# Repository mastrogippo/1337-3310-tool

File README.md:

## Nokia 3310 converted to a multitool
### More info:

http://hackaday.io/project/3472-1337-3310-tool

http://www.mastrogippo.it/

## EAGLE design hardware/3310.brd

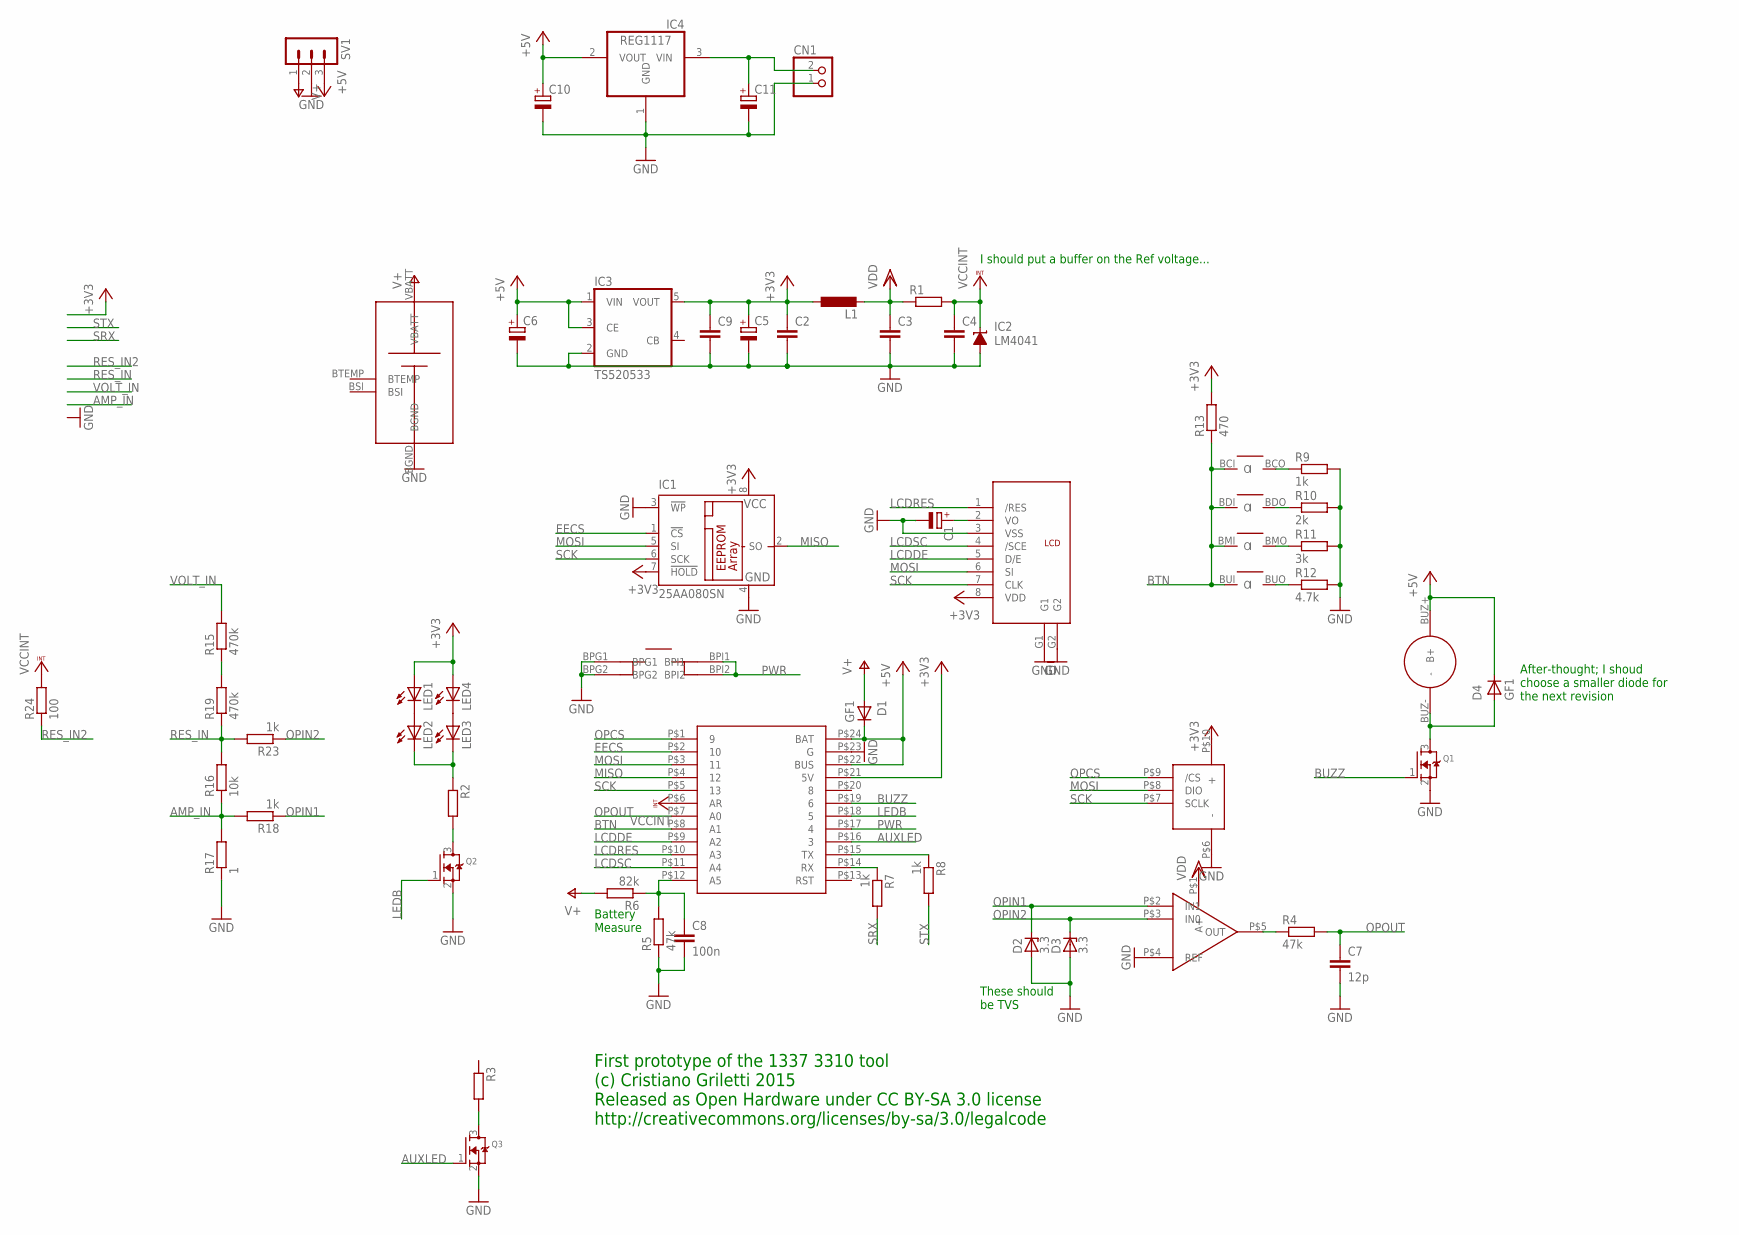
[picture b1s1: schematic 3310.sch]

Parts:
C1: CPOL-EUC/6032-28R; C/6032-28R
C2, C3, C4, C9: C-EUC0805K; C0805K
C5, C6, C10, C11: CPOL-EUB/3528-21R; B/3528-21R
C7: 12p; C0805K
C8: 100n; C0805K
CN1: JST_2PIN-SMT; JST-PH-2-SMT
D1, D4: GF1; SMA-DO214AC
D2, D3: 3.3; SOD80C
IC1: 25AA080SN; SO-08
IC2: LM4041; DBZ_R-PDSO-G3
IC3: TS520533; SOT25
IC4: REG1117; SOT223
L1: L-EUL3216C; L3216C
LED1, LED2, LED3, LED4: LEDCHIPLED_0603; CHIPLED_0603
Q1, Q2, Q3: MOSFET-NREFLOW; SOT23
R1, R2, R3: R-EU_R0805; R0805
R4, R5: 47k; R0805
R6: 82k; R0805
R7, R8, R9, R18, R23: 1k; R0805
R10: 2k; R0805
R11: 3k; R0805
R12: 4.7k; R0805
R13: 470; R0805
R15, R19: 470k; R0805
R16: 10k; R0805
R17: 1; R0805
R24: 100; R0805
SV1: MA03-1
U$1: 3310PANEL_NONUM; 3310BRD_NONUM
U$2: PGA113; VSSOP
U$3: TRINKET

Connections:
+3V3: C2.1, C5.+, C9.1, IC1.7 (!HOLD), IC1.8 (VCC), IC3.5 (VOUT), L1.1, LED1.A, LED4.A, R13.2, U$1.8 (VDD), U$2.P$10 (+), U$3.P$21 (5V)
+5V: C6.+, C10.+, D1.K (C), D4.K (C), IC3.1 (VIN), IC3.3 (CE), IC4.2 (VOUT), SV1.3, U$1.BUZ+ (B+), U$3.P$22 (BUS), U$3.P$24 (BAT)
AMP_IN: R16.1, R17.2, R18.2
AUXLED: Q3.1 (G), U$3.P$16 (3)
BTN: R13.1, U$1.BCI (I), U$1.BDI (I), U$1.BMI (I), U$1.BUI (I), U$3.P$8 (A1)
BUZZ: Q1.1 (G), U$3.P$19 (6)
EECS: IC1.1 (!CS), U$3.P$2 (10)
GND: C1.-, C2.2, C3.2, C4.2, C5.-, C6.-, C7.2, C8.2, C9.2, C10.-, C11.-, CN1.1 (2), D2.A, D3.A, IC1.3 (!WP), IC1.4 (GND), IC2.2 (A), IC3.2 (GND), IC4.1 (GND), Q1.2 (S), Q2.2 (S), Q3.2 (S), R5.1, R9.2, R10.2, R11.2, R12.2, R17.1, SV1.2, U$1.3 (VSS), U$1.BGND, U$1.BPG1, U$1.BPG2, U$1.G1, U$1.G2, U$2.P$4 (REF), U$2.P$6 (-), U$3.P$23 (G)
LCDDE: U$1.5 (D/E), U$3.P$9 (A2)
LCDRES: U$1.1 (/RES), U$3.P$10 (A3)
LCDSC: U$1.4 (/SCE), U$3.P$11 (A4)
LEDB: Q2.1 (G), U$3.P$18 (5)
MISO: IC1.2 (SO), U$3.P$4 (12)
MOSI: IC1.5 (SI), U$1.6 (SI), U$2.P$8 (DIO), U$3.P$3 (11)
unnamed: C1.+, U$1.2 (VO)
unnamed: R4.1, U$2.P$5 (OUT)
unnamed: C8.1, R5.2, R6.1, U$3.P$12 (A5)
unnamed: D4.A, Q1.3 (D), U$1.BUZ- (-)
unnamed: R8.1, U$3.P$15 (TX)
unnamed: R7.1, U$3.P$14 (RX)
unnamed: Q2.3 (D), R2.2
unnamed: R9.1, U$1.BCO (O)
unnamed: R10.1, U$1.BDO (O)
unnamed: R11.1, U$1.BMO (O)
unnamed: R12.1, U$1.BUO (O)
unnamed: R15.1, R19.2
unnamed: LED1.C, LED2.A
unnamed: LED3.A, LED4.C
unnamed: LED2.C, LED3.C, R2.1
unnamed: Q3.3 (D), R3.2
unnamed: C11.+, CN1.2 (1), IC4.3 (VIN)
OPCS: U$2.P$9 (/CS), U$3.P$1 (9)
OPIN1: D2.C, R18.1, U$2.P$2 (IN1)
OPIN2: D3.C, R23.1, U$2.P$3 (IN0)
OPOUT: C7.1, R4.2, U$3.P$7 (A0)
PWR: U$1.BPI1, U$1.BPI2, U$3.P$17 (4)
RES_IN: R16.2, R19.1, R23.2
RES_IN2: R24.1
SCK: IC1.6 (SCK), U$1.7 (CLK), U$2.P$7 (SCLK), U$3.P$5 (13)
SRX: R7.2
STX: R8.2
V+: D1.A, R6.2, SV1.1, U$1.VBATT
VCCINT: C4.1, IC2.1 (C), R1.2, R24.2, U$3.P$6 (AR)
VDD: C3.1, L1.2, R1.1, U$2.P$1 (A+)
VOLT_IN: R15.2

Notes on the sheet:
Battery Measure
I should put a buffer on the Ref voltage...
After-thought; I shoud choose a smaller diode for the next revision
First prototype of the 1337 3310 tool (c) Cristiano Griletti 2015 Released as Open Hardware under CC BY-SA 3.0 license http://creativecommons.org/licenses/by-sa/3.0/legalcode
These should be TVS

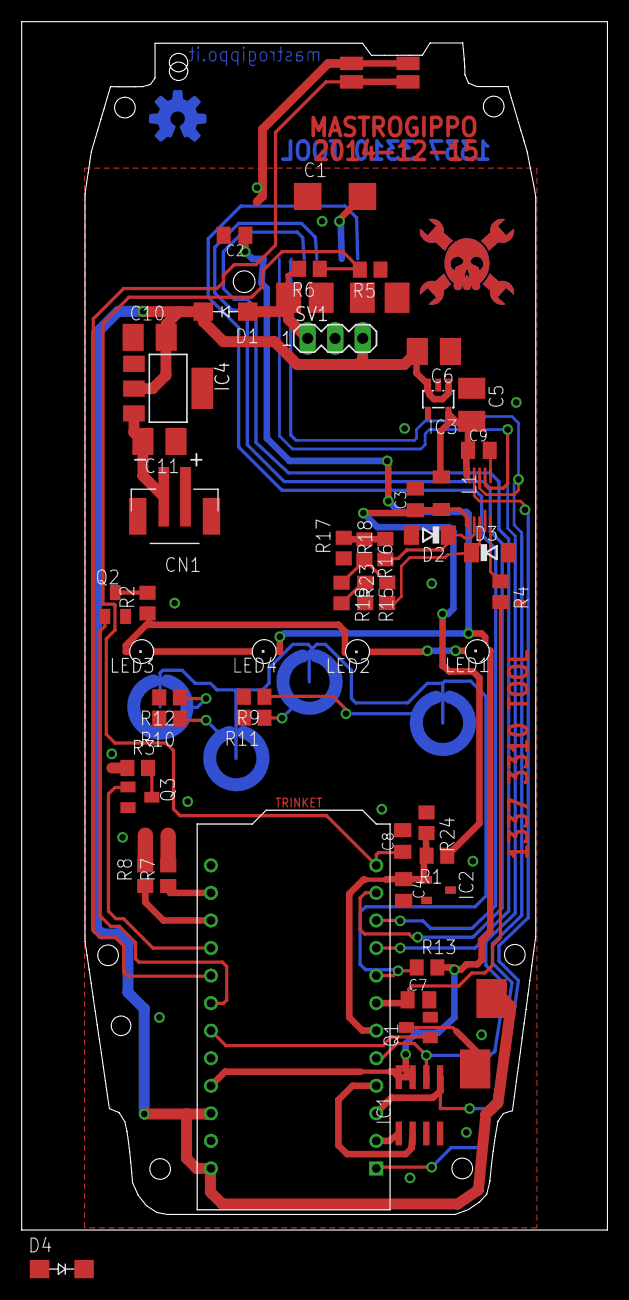
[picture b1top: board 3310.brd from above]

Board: 2 copper layers, 54.0 x 111.4 mm, 52 parts (1 on the bottom side), 41 nets.

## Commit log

2015-01-02 :octocat: Added .gitattributes & .gitignore files
2015-01-03 Added hardware design files
